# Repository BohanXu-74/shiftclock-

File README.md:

# Seven Segment Clock

A 4-digit seven segment clock built with an STC15W204S microcontroller and DS1302 RTC module. Uses shift registers and multiplexing to drive the display with minimal pins. Runs a state machine for time, alarm, and timer modes. Features custom debounce logic, a self-written stc15.h header, and a KiCad PCB design in progress.

---

## Hardware

| Component | Description |
|---|---|
| STC15W204S | Main microcontroller |
| DS1302 | Real-time clock module for timekeeping |
| 4-digit 7-segment display | Output display |
| Shift register | Used to load BCD segment data |
| Push buttons | Mode selection and value adjustment |

---

## How It Works

The MCU constantly refreshes the display by rapidly switching between each of the 4 digits while the shift register loads in the BCD code for the seven segment. The digits switch fast enough that all 4 appear to be on at the same time.

The clock runs on a state machine that cycles through three modes:

- **Time** — displays current time from the DS1302 RTC
- **Alarm** — supports up to 16 individually configurable alarms
- **Timer** — user-configurable countdown timer

Before entering each mode, the display shows the mode name first instead of instantly switching to numbers.

---

## Software

- Written in C
- Custom `stc15.h` header file written from scratch since no existing one was available for this MCU
- Custom button debounce logic to prevent multiple registrations from a single press
- Timing logic and display refresh written manually to eliminate flickering

---

## Files

| File | Description |
|---|---|
| `main.c` | Full source code |
| `clock.kicad_pcb` | KiCad PCB layout |
| `clock-cache.lib` | KiCad component cache |
| `stc15.h` | Custom SFR header for STC15W204S |

---

## Status

Currently working on a prototype breadboard/perf board setup. PCB design in KiCad is in progress. Final goal is a custom PCB version in an enclosure.

---

## Notes

- KiCad version used: v5.1 (older PC limitation)
- Hackaday project page: [DIY Seven Segment Clock](https://hackaday.io/project/205699-diy-seven-segment-clock)

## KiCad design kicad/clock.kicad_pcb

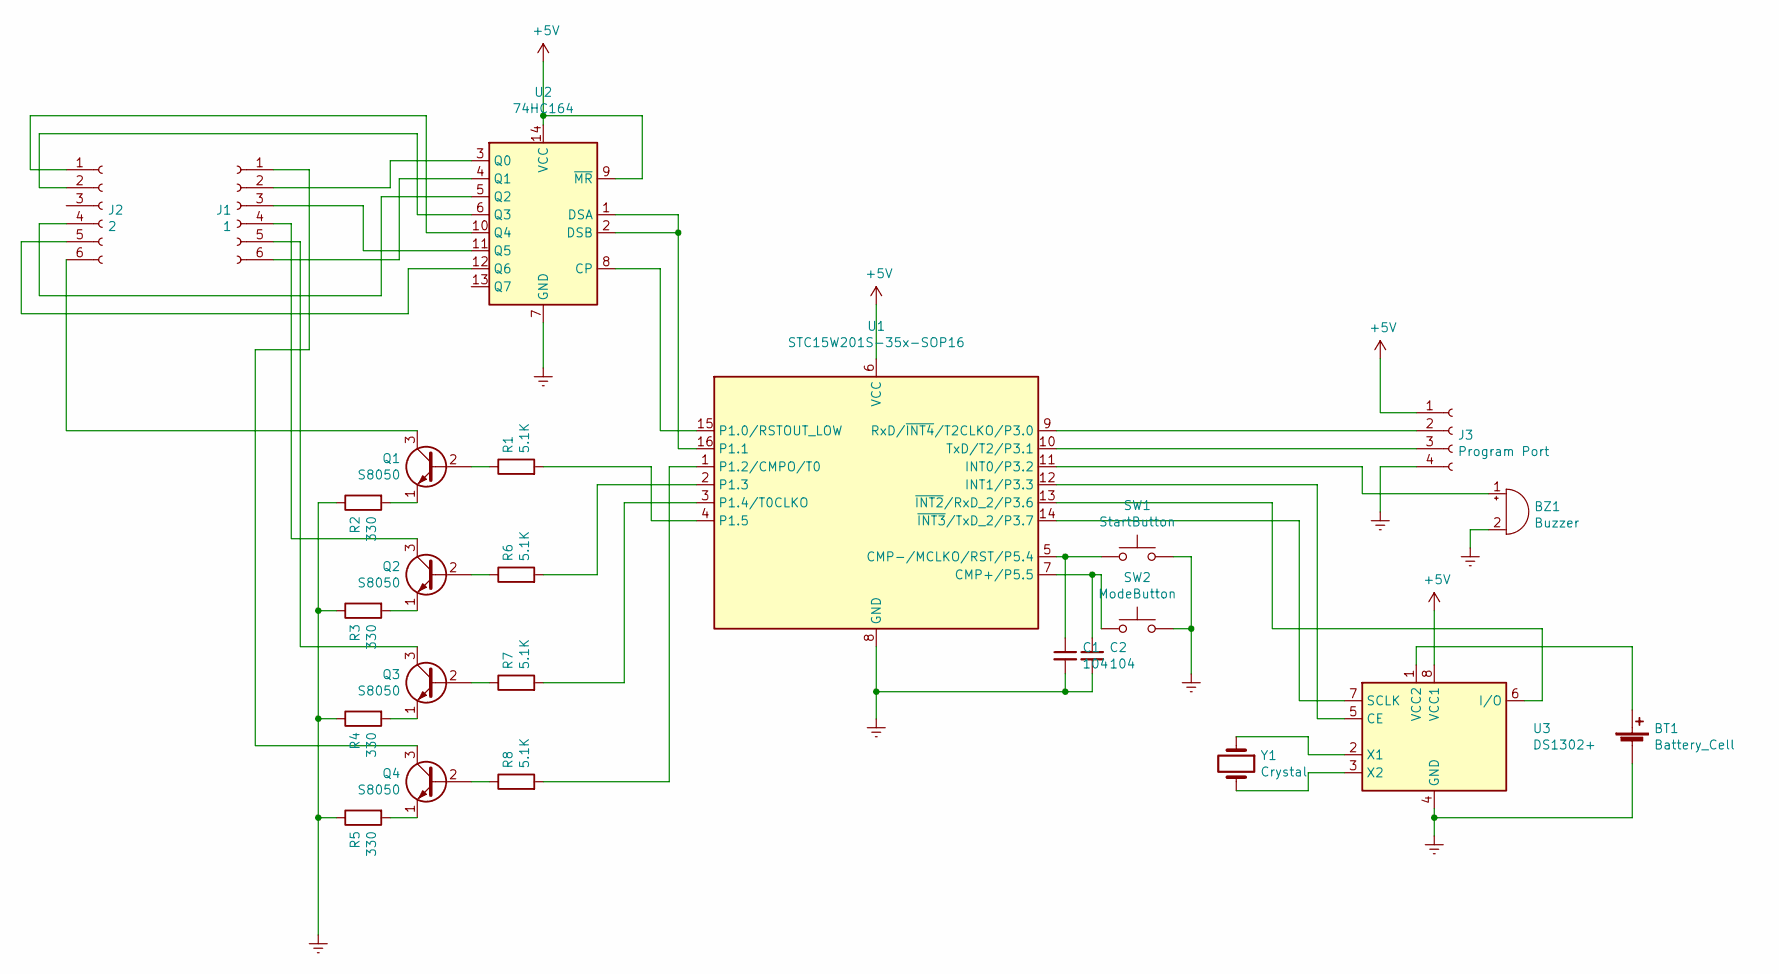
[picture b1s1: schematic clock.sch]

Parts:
BT1: Battery_Cell; BatteryHolder_ComfortableElectronic_CH273-2450_1x2450
BZ1: Buzzer; MagneticBuzzer_ProSignal_ABT-410-RC
C1, C2: 104; C_Disc_D4.7mm_W2.5mm_P5.00mm
J1: 1; PinSocket_1x06_P2.54mm_Vertical
J2: 2; PinSocket_1x06_P2.54mm_Vertical
J3: Program Port; PinSocket_1x04_P2.54mm_Vertical
Q1, Q2, Q3, Q4: S8050; TO-92_Inline
R1, R6, R7, R8: 5.1K; R_0805_2012Metric_Pad1.15x1.40mm_HandSolder
R2, R3, R4, R5: 330; R_0805_2012Metric_Pad1.15x1.40mm_HandSolder
SW1: StartButton; SW_PUSH_6mm_H7.3mm
SW2: ModeButton; SW_PUSH_6mm_H7.3mm
U1: STC15W201S-35x-SOP16; DIP-16_W7.62mm
U2: 74HC164; DIP-14_W7.62mm_Socket
U3: DS1302+; DIP-8_W7.62mm
Y1: Crystal; Crystal_HC51-U_Vertical

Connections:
+5V: J3.1, U1.6 (VCC), U2.9 (~MR), U2.14 (VCC), U3.8 (VCC1)
Earth: BT1.2 (-), BZ1.2 (+), C1.2, C2.2, J3.4, R2.1, R3.1, R4.1, R5.1, SW1.2, SW2.2, U1.8 (GND), U2.7 (GND), U3.4 (GND)
unnamed: BT1.1 (+), U3.1 (VCC2)
unnamed: BZ1.1 (-), U1.11 (INT0/P3.2)
unnamed: C1.1, SW1.1, U1.5 (CMP-/MCLKO/RST/P5.4)
unnamed: C2.1, SW2.1, U1.7 (CMP+/P5.5)
unnamed: J1.1, Q4.3 (C)
unnamed: J1.2, U2.3 (Q0)
unnamed: J1.3, U2.11 (Q5)
unnamed: J1.4, Q2.3 (C)
unnamed: J1.5, Q3.3 (C)
unnamed: J1.6, U2.4 (Q1)
unnamed: J2.1, U2.10 (Q4)
unnamed: J2.2, U2.6 (Q3)
unnamed: J2.4, U2.5 (Q2)
unnamed: J2.5, U2.12 (Q6)
unnamed: J2.6, Q1.3 (C)
unnamed: J3.2, U1.9 (RxD/~INT4~/T2CLKO/P3.0)
unnamed: J3.3, U1.10 (TxD/T2/P3.1)
unnamed: Q1.1 (E), R2.2
unnamed: Q1.2 (B), R1.1
unnamed: Q2.1 (E), R3.2
unnamed: Q2.2 (B), R6.1
unnamed: Q3.1 (E), R4.2
unnamed: Q3.2 (B), R7.1
unnamed: Q4.1 (E), R5.2
unnamed: Q4.2 (B), R8.1
unnamed: R1.2, U1.4 (P1.5)
unnamed: R6.2, U1.2 (P1.3)
unnamed: R7.2, U1.3 (P1.4/T0CLKO)
unnamed: R8.2, U1.1 (P1.2/CMPO/T0)
unnamed: U1.12 (INT1/P3.3), U3.5 (CE)
unnamed: U1.13 (~INT2~/RxD_2/P3.6), U3.6 (I/O)
unnamed: U1.14 (~INT3~/TxD_2/P3.7), U3.7 (SCLK)
unnamed: U1.15 (P1.0/RSTOUT_LOW), U2.8 (CP)
unnamed: U1.16 (P1.1), U2.1 (DSA), U2.2 (DSB)
unnamed: U3.2 (X1), Y1.1
unnamed: U3.3 (X2), Y1.2

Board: 2 copper layers, 25 parts (0 on the bottom side), 38 nets, no tracks yet.

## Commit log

2026-05-14 Update shift register reference to 74HC164
2026-05-14 Rename 1000004734.jpg to image.jpg
2026-05-14 Rename main.c to src/main.c
